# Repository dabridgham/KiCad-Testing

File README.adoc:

= KiCad Testing

Just a little test board to show up a possible bug in KiCad.

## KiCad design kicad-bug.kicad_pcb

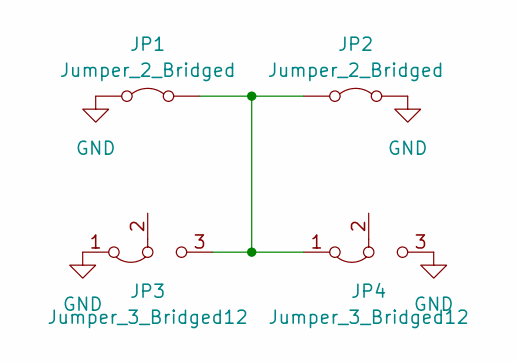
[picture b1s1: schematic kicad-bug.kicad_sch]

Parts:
JP1, JP2: Jumper_2_Bridged; SolderJumper-2_P1.3mm_Bridged_RoundedPad1.0x1.5mm
JP3, JP4: Jumper_3_Bridged12; SolderJumper-3_P1.3mm_Bridged12_RoundedPad1.0x1.5mm

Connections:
GND: JP1.1 (A), JP2.2 (B), JP3.1 (A), JP4.3 (B)
unnamed: JP1.2 (B), JP2.1 (A), JP3.3 (B), JP4.1 (A)

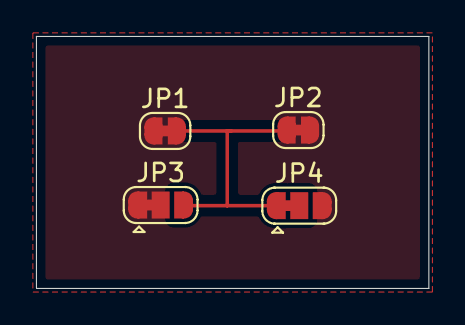
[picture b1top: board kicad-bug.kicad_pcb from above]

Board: 2 copper layers, 21.8 x 14.0 mm, 4 parts (0 on the bottom side), 2 nets.

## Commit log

2025-02-26 after poking around with filling zones and running DRC
